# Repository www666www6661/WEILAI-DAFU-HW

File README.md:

# DAFU

未来战队自研大符硬件方案，通过四通道半桥称重传感器采集正向毫秒级冲击波形，为环数检测提供信号。电路采用 **TLC2274A 缓冲、INA180A4 放大与 STM32F030 ADC 采集**，当前 PCB 版本为 **DAFU-DEMO-V0.2.1**。

## PCB 预览

## 主要参数

| 项目 | 详情 |
| :-- | --- |
| 输入通道 | 4 路三线半桥称重传感器 |
| 目标传感器 | 50 kg，1 mV/V，半桥总阻值 2 kΩ（1 kΩ / 1 kΩ） |
| 电源输入 / 传感器激励 | 5 V |
| 数字电源 | ME6206A33XG 输出 3.3 V |
| 模拟前端 | TLC2274AIDR 四路缓冲，INA180A4 差分增益 200 V/V |
| 基准缓冲 | UMW OPA333AIDBVR，5 V 供电 |
| 主控 | STM32F030C6Tx，LQFP-48 |
| 传感器接口 | J1–J4，JST GH 1.25 mm，3 Pin，卧贴 |
| 调试接口 | J5，Molex CLIK-Mate 1.25 mm，4 Pin，卧贴 |
| PCB 尺寸 | 30.0 × 31.6 mm，四角各 1 mm 倒角，面积 946.0 mm² |
| PCB 层数 / 厚度 | 双层 / 1.6 mm |
| 装配 | 42 个实际装配元件，均在正面；底面仅有复位测试焊盘 |

本仓库包含硬件工程和生产资料。冲击采样率、触发、波形存储和传输需要固件实现，当前资料未包含实测冲击响应、噪声或有效分辨率结论。

## 接口与测试点

接线请按焊盘编号核对，线束颜色和观察连接器的方向不能代替引脚定义。

| 接口 | 引脚 | 功能 / 网络 |
| --- | --- | --- |
| J1–J4：传感器接口 | 1 | +5V，传感器激励正极 |
| J1–J4：传感器接口 | 2 | IN1–IN4，对应通道的半桥中点信号 |
| J1–J4：传感器接口 | 3 | GND，传感器激励负极 |
| J1–J4 | MP | 连接器固定焊盘，接 GND |
| J5：SWD 调试接口 | 1 | SWDIO |
| J5：SWD 调试接口 | 2 | SWCLK |
| J5：SWD 调试接口 | 3 | GND |
| J5：SWD 调试接口 | 4 | +3.3V，经 R19 = 0 Ω 连接 |
| J5 | MP | 连接器固定焊盘，接 GND |
| TP1：正面电源焊盘 | 1 | +5V 输入 |
| TP2：正面电源焊盘 | 1 | GND |
| TP5：底面测试点 | 1 | NRST |
| TP6：底面测试点 | 1 | GND_RST，接 GND |

J5 使用 Molex CLIK-Mate 封装，与 J1–J4 的 GH 插座并非同一连接器系列。TP5 与 TP6 用于复位操作。

## 电路与采集

每路传感器中点信号先经 U6 电压跟随器缓冲，再由 INA180A4 相对公共基准放大。R9、R10 和 R12 将基准设置在 5 V 中点略下方，U9 对其缓冲，为正向信号保留输出余量。各路放大输出经 100 Ω 串联电阻送至 MCU 的 PA3、PA4、PA5、PA6。

按 5 V 激励、传感器灵敏度 1 mV/V 计算，50 kg 标称满量程对应约 5 mV 的输入变化，经过 200 倍放大后约为 1 V 的输出变化。理想无载基线约为 1.55 V，正向满量程约为 2.55 V；实际基线和量程仍需根据传感器零点、器件误差和装配结果校准。传感器接线方向应使目标冲击导致中点电压上升。

四路信号接入同一 MCU ADC，采样时序由固件配置。这些参数描述当前电路的标称关系，不代表已验证的动态测量性能。

## 主要器件

以下数量为单板用量。完整清单见 [生产 BOM](production/dafu/assembly/DAFU-BOM.csv)，采购时同时核对型号、封装和制造商。

| 位号 | 数量 | 型号 / 参数 | 封装 / 说明 |
| --- | --- | --- | --- |
| U1、U3、U4、U5 | 4 | INA180A4，增益 200 V/V | SOT-23-5 |
| U2 | 1 | STM32F030C6Tx | LQFP-48，当前 PCB 使用自定义焊盘版本 |
| U6 | 1 | Texas Instruments TLC2274AIDR | SOIC-14，四运放 |
| U7 | 1 | ME6206A33XG | SOT-23-3，3.3 V LDO |
| U9 | 1 | UMW OPA333AIDBVR | SOT-23-5，须匹配工程中的制造商和引脚定义 |
| J1–J4 | 4 | JST GH，1.25 mm，3 Pin，卧贴 | SM03B-GHS-TB 对应封装 |
| J5 | 1 | Molex CLIK-Mate，1.25 mm，4 Pin，卧贴 | 502386-0470 对应封装 |
| R5、R6 | 2 | 10 kΩ | 0603 |
| R9、R10、R11 | 3 | 5.1 kΩ | 0603 |
| R12 | 1 | 820 kΩ | 0603 |
| R13–R16 | 4 | 100 Ω | 0603，ADC 输入串联电阻 |
| R19 | 1 | 0 Ω | 0603 |
| C1–C9、C12、C13、C20、C21 | 13 | 100 nF | 0603 |
| C14、C15、C24、C25 | 4 | 10 µF | 0805 |
| D1 | 1 | LED | 0603 |
| C11 | 不装 | 100 nF | DNP，保留 PCB 焊盘与开窗 |

TP1、TP2、TP5、TP6 为裸 PCB 焊盘，不计入采购及贴装数量。

## 制造资料

```text
.
├── DAFU.kicad_pro                 KiCad 工程
├── DAFU.kicad_sch                 原理图
├── DAFU.kicad_pcb                 PCB
├── DAFU_Local.kicad_sym           项目本地符号库
├── DAFU_PCB.pretty/               项目本地封装库
├── docs/images/                   PCB 双面预览
└── production/                    制造资料
    ├── dafu.zip                   完整生产压缩包
    ├── dafu.zip.sha256            完整包 SHA-256
    ├── dafu-gerbers.zip           单独打板包
    ├── dafu-gerbers.zip.sha256     打板包 SHA-256
    └── dafu/
        ├── gerbers/               Gerber、钻孔与钻孔报告
        ├── assembly/              BOM、贴装坐标与装配图
        ├── previews/              铜层、丝印及 3D 预览
        ├── documentation/         DRC、ERC、板数据及导出说明
        └── manifest.json          源文件和输出文件校验值
```

工程使用 KiCad 10.0.5。项目符号库与封装库通过 `${KIPRJMOD}` 引用，3D 模型使用 KiCad 标准模型目录。制造文件根据 2026-10-12 保存的工程导出，底层 GND 为实心直连铺铜，保留 279 个原生泪滴。Gerber 无需镜像。

本版检查结果为 ERC 0 项、活动 PCB DRC 违规 0 项、未连接 0 项。保留的原理图一致性警告包括 C11 的 DNP 属性不同步，以及 U2 缺少 10、17、18、19 号焊盘；这四脚在原理图中均标注 No Connect，在当前 PCB 中没有铜焊盘、阻焊或锡膏开窗。另有一项既有的 U2 封装库不匹配排除项。详细记录见 [生产说明](production/dafu/README.md) 和 [检查资料](production/dafu/documentation/)。

C11 按原理图不装，贴装文件包含 42 个正面元件，底面无贴装元件。原始 PCB 上 C11 的焊盘、阻焊和锡膏开窗予以保留；贴装时应以 BOM 的 DNP 标记和装配图为准。

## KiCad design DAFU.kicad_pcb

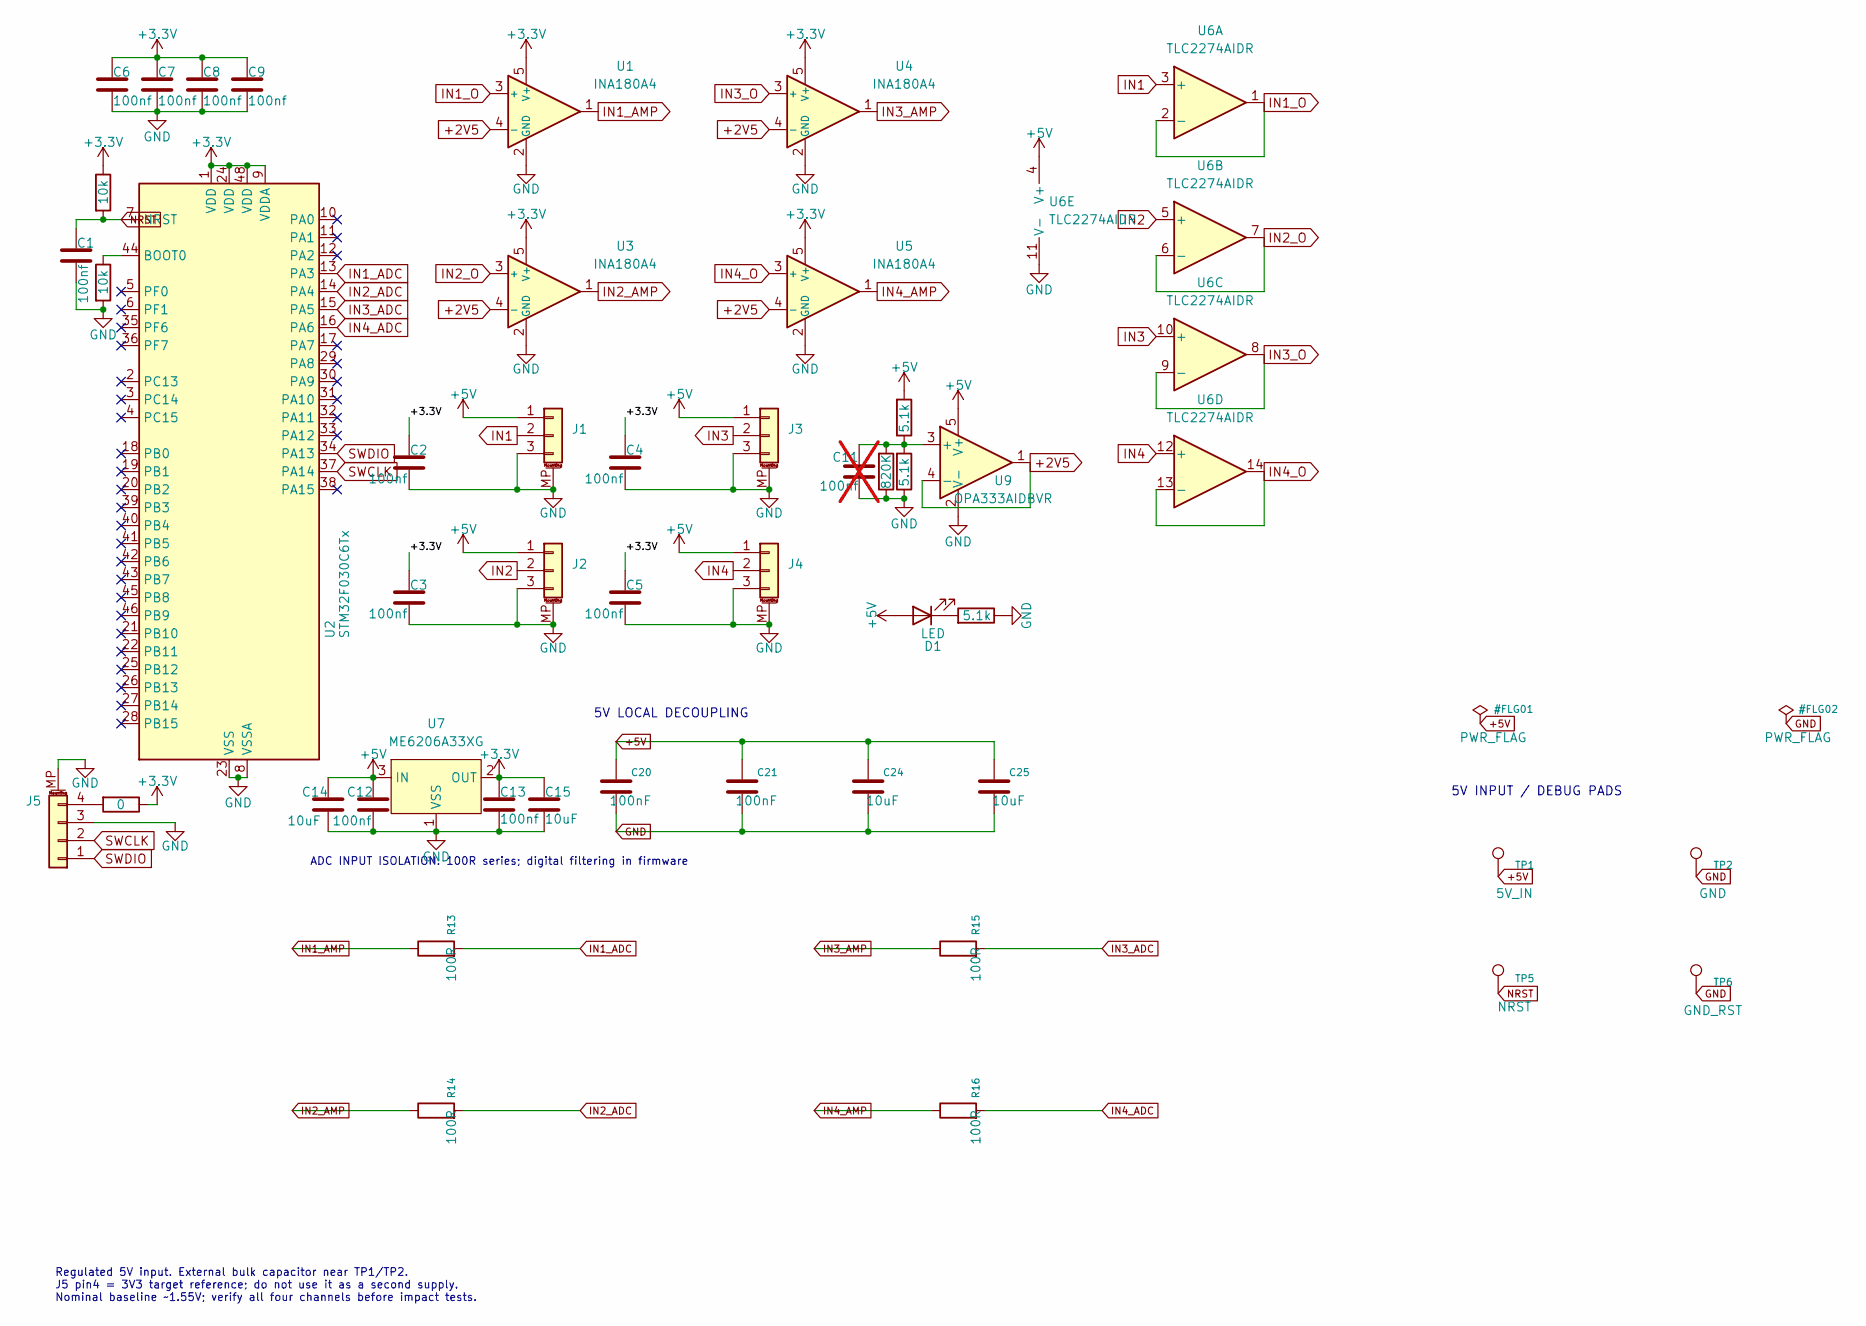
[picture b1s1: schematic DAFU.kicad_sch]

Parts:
C1, C2, C3, C4, C5, C6, C7, C8, C9, C12, C13: 100nf; C_0603_1608Metric
C11: 100nf; C_0603_1608Metric; not fitted
C14, C15, C24, C25: 10uF; C_0805_2012Metric; Voltage 16V
C20, C21: 100nF; C_0603_1608Metric
D1: LED; LED_0603_1608Metric
J1, J2, J3, J4: Conn_01x03_MountingPin; JST_GH_SM03B-GHS-TB_1x03-1MP_P1.25mm_Horizontal
J5: Conn_01x04; Molex_CLIK-Mate_502386-0470_1x04-1MP_P1.25mm_Horizontal
R5, R6: 10k; R_0603_1608Metric
R9, R10: 5.1k; R_0603_1608Metric; Tolerance 0.1%
R11: 5.1k; R_0603_1608Metric
R12: 820K; R_0603_1608Metric
R13, R14, R15, R16: 100R; R_0603_1608Metric
R19: 0; R_0603_1608Metric
TP1: 5V_IN; SolderWire_Pad_2.5x2.5mm
TP2: GND; SolderWire_Pad_2.5x2.5mm
TP5: NRST; TestPoint_Pad_D1.5mm
TP6: GND_RST; TestPoint_Pad_D1.5mm
U1, U3, U4, U5: INA180A4; SOT-23-5
U2: STM32F030C6Tx; LQFP-48_7x7mm_P0.5mm
U6: TLC2274AIDR; SOIC-14_3.9x8.7mm_P1.27mm; MPN TLC2274AIDR
U7: ME6206A33XG; SOT-23-3
U9: OPA333AIDBVR; SOT-23-5; MPN OPA333AIDBVR

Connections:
+2V5: U1.4 (-), U3.4 (-), U4.4 (-), U5.4 (-), U9.1, U9.4 (-)
+3.3V: C2.1, C3.1, C4.1, C5.1, C6.1, C7.1, C8.1, C9.1, C13.1, C15.1, R6.1, R19.1, U1.5 (V+), U2.1 (VDD), U2.9 (VDDA), U2.24 (VDD), U2.48 (VDD), U3.5 (V+), U4.5 (V+), U5.5 (V+), U7.2 (OUT)
+5V: C12.1, C14.1, C20.1, C21.1, C24.1, C25.1, D1.2 (A), J1.1, J2.1, J3.1, J4.1, R9.2, TP1.1, U6.4 (V+), U7.3 (IN), U9.5 (V+)
GND: C1.2, C2.2, C3.2, C4.2, C5.2, C6.2, C7.2, C8.2, C9.2, C11.2, C12.2, C13.2, C14.2, C15.2, C20.2, C21.2, C24.2, C25.2, J1.3, J1.MP (MountPin), J2.3, J2.MP (MountPin), J3.3, J3.MP (MountPin), J4.3, J4.MP (MountPin), J5.3, J5.MP (MountPin), R5.2, R10.1, R11.1, R12.1, TP2.1, TP6.1, U1.2 (GND), U2.8 (VSSA), U2.23 (VSS), U2.47 (VSS), U3.2 (GND), U4.2 (GND), U5.2 (GND), U6.11 (V-), U7.1 (VSS), U9.2 (V-)
IN1: J1.2, U6.3 (+)
IN1_ADC: R13.2, U2.13 (PA3)
IN1_AMP: R13.1, U1.1
IN1_O: U1.3 (+), U6.1, U6.2 (-)
IN2: J2.2, U6.5 (+)
IN2_ADC: R14.2, U2.14 (PA4)
IN2_AMP: R14.1, U3.1
IN2_O: U3.3 (+), U6.6 (-), U6.7
IN3: J3.2, U6.10 (+)
IN3_ADC: R15.2, U2.15 (PA5)
IN3_AMP: R15.1, U4.1
IN3_O: U4.3 (+), U6.8, U6.9 (-)
IN4: J4.2, U6.12 (+)
IN4_ADC: R16.2, U2.16 (PA6)
IN4_AMP: R16.1, U5.1
IN4_O: U5.3 (+), U6.13 (-), U6.14
NRST: C1.1, R6.2, TP5.1, U2.7 (NRST)
unnamed: D1.1 (K), R11.2
unnamed: J5.4, R19.2
unnamed: R5.1, U2.44 (BOOT0)
unnamed: C11.1, R9.1, R10.2, R12.2, U9.3 (+)
SWCLK: J5.2, U2.37 (PA14)
SWDIO: J5.1, U2.34 (PA13)

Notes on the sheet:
5V INPUT / DEBUG PADS
ADC INPUT ISOLATION: 100R series; digital filtering in firmware
5V LOCAL DECOUPLING
Regulated 5V input. External bulk capacitor near TP1/TP2. J5 pin4 = 3V3 target reference; do not use it as a second supply. Nominal baseline ~1.55V; verify all four channels before impact tests.

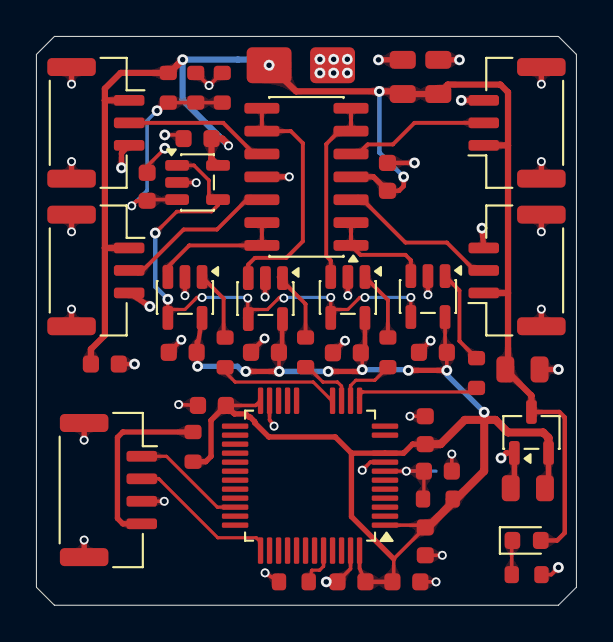
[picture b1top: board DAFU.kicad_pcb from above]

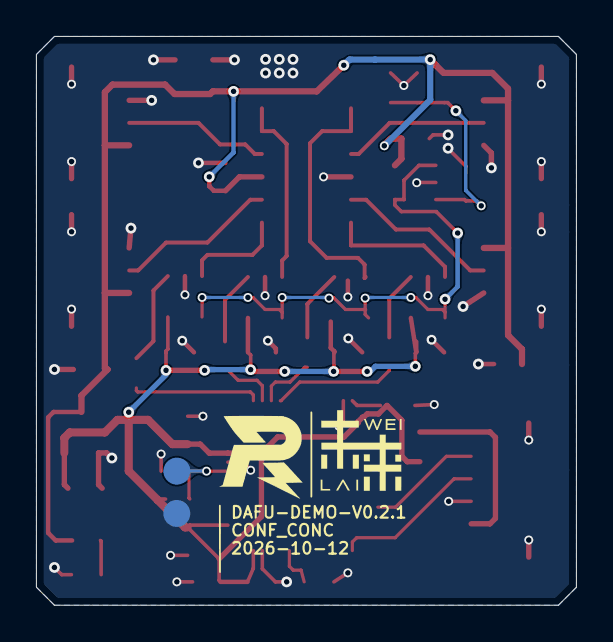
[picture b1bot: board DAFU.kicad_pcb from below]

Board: 2 copper layers, 30.0 x 31.6 mm, 47 parts (2 on the bottom side), 27 nets.

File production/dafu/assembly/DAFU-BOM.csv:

References,Quantity_per_board,Value,Footprint,Manufacturer,MPN,Assembly_Status
"C1, C2, C3, C4, C5, C6, C7, C8, C9, C12, C13",11,100nf,DAFU_PCB:C_0603_1608Metric,,,Populate
C11,1,100nf,DAFU_PCB:C_0603_1608Metric,,,DNP
"C14, C15, C24, C25",4,10uF,DAFU_PCB:C_0805_2012Metric,,,Populate
"C20, C21",2,100nF,DAFU_PCB:C_0603_1608Metric,,,Populate
D1,1,LED,LED_SMD:LED_0603_1608Metric,,,Populate
"J1, J2, J3, J4",4,Conn_01x03_MountingPin,Connector_JST:JST_GH_SM03B-GHS-TB_1x03-1MP_P1.25mm_Horizontal,,,Populate
J5,1,Conn_01x04,Connector_Molex:Molex_CLIK-Mate_502386-0470_1x04-1MP_P1.25mm_Horizontal,,,Populate
"R5, R6",2,10k,DAFU_PCB:R_0603_1608Metric,,,Populate
"R9, R10, R11",3,5.1k,DAFU_PCB:R_0603_1608Metric,,,Populate
R12,1,820K,DAFU_PCB:R_0603_1608Metric,,,Populate
"R13, R14, R15, R16",4,100R,DAFU_PCB:R_0603_1608Metric,,,Populate
R19,1,0,DAFU_PCB:R_0603_1608Metric,,,Populate
TP1,1,5V_IN,DAFU_PCB:SolderWire_Pad_2.5x2.5mm,,,PCB pad
TP2,1,GND,DAFU_PCB:SolderWire_Pad_2.5x2.5mm,,,PCB pad
TP5,1,NRST,DAFU_PCB:TestPoint_Pad_D1.5mm,,,PCB pad
TP6,1,GND_RST,DAFU_PCB:TestPoint_Pad_D1.5mm,,,PCB pad
"U1, U3, U4, U5",4,INA180A4,Package_TO_SOT_SMD:SOT-23-5,,,Populate
U2,1,STM32F030C6Tx,Package_QFP:LQFP-48_7x7mm_P0.5mm,,,Populate
U6,1,TLC2274AIDR,Package_SO:SOIC-14_3.9x8.7mm_P1.27mm,Texas Instruments,TLC2274AIDR,Populate
U7,1,ME6206A33XG,Package_TO_SOT_SMD:SOT-23-3,,,Populate
U9,1,OPA333AIDBVR,Package_TO_SOT_SMD:SOT-23-5,UMW,OPA333AIDBVR,Populate
